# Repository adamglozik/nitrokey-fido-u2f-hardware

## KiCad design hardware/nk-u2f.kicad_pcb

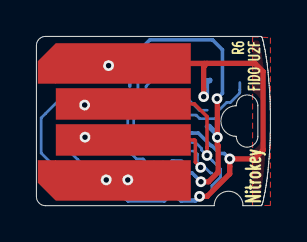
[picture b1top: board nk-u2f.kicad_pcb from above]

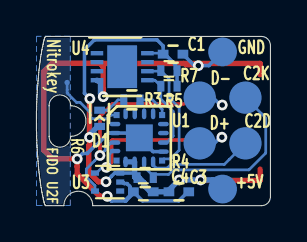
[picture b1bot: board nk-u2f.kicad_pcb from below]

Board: 2 copper layers, 13.0 x 9.4 mm, 14 parts (13 on the bottom side), 11 nets.

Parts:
C1, C4: 0.1uF; C_0402
C3: 4.7uF; C_0402
D1: LED_Small; LED_0402
J1: USB_Plug; USB-PCB
J2: prog_conn_nk
P1: TouchPAD; TouchPad
R3: 100; R_0402
R4, R5, R7: 4K7; R_0402
U1: EFM8UB30F40G-A; QFN-20-0.5mm-user
U3: DF5A5.6JE; SOT-553
U4: ATECC508A; DFN-8-1EP_3x3mm_Pitch0.5mm

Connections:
/+5V: C1.1, C3.1, C4.1, D1.2, J1.1, J2.1, R4.1, R5.1, R7.1, U1.7, U1.8, U3.3, U4.8
/Button: P1.1, U1.1
/C2CK: J2.4, R4.2, U1.9
/C2D: J2.5, U1.10
/GND: C1.2, C3.2, C4.2, J1.4, J2.6, U1.3, U1.12, U1.21, U3.2, U4.4
/HD+: J1.3, J2.2, U1.4, U3.5
/HD-: J1.2, J2.3, U1.5, U3.4
/LED: R3.1, U1.16
/SCL: R7.2, U1.11, U4.6
/SDA: R5.2, U1.13, U4.5
unnamed: D1.1, R3.2

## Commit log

2018-07-19 REV6 - MTCH101 touch controller IC replaced with a simplier capacitive voltage divider solution. - Board size shrunken to fit inside an USB A socket
